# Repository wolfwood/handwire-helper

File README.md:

# Handwire Helpers

A collection of PCBs aimed at supporting handwired dactyl-ish keyboards. The goal is faster, simpler assembly (by offloading the key matrix from the handwiring to the PCB) and flexibility in placement of keys and connectors.

## Matrix PCBs

### Handwire Helper
Supports 8 columns, 4 rows for the first six columns and 5 for the last 2 (thumb) columns.  The first row is the pin towards the microcontroller connections (narrow side). On the MCU side there are 8 pins for the columns and 5 for the rows, with the final pin as an (unnecessary) ground.

The intent is to connect keyswitches to the PCB using hotswap sockets, soldered to [ribbon cables with DuPont connectors on the other side](https://www.adafruit.com/product/3141), which can plug in to the header on the long side of the PCB.

This lets the keyspacing be determined by a 3D printed case, independent of the PCB, so that electronics can be reused as keyboard designs change. This also means that different switch types can be supported, without prior consideration in the PCB design.

The microcontroller can be similarly connected to this board by jumpers, allowing flexibility in case design, and in placement of the USB plug.

Version 0.1 has been successfully manufactured and functionality has been tested and verified.

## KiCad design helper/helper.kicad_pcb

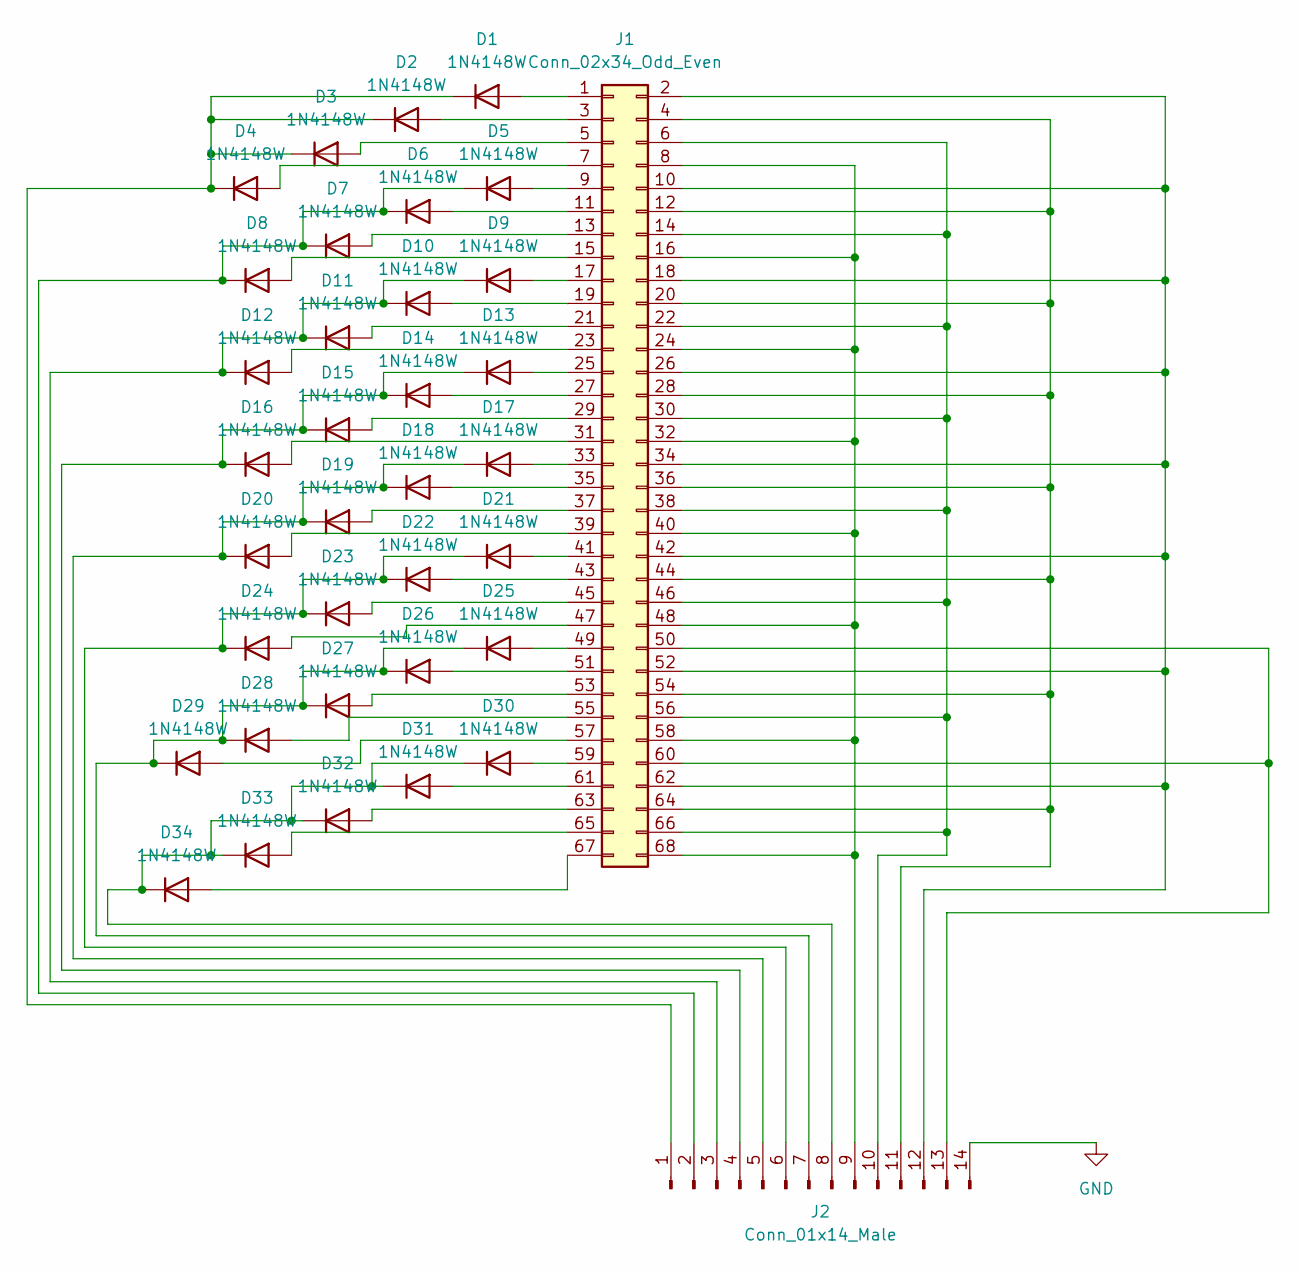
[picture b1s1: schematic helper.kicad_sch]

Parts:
D1, D2, D3, D4, D5, D6, D7, D8, D9, D10, D11, D12, D13, D14, D15, D16, D17, D18, D19, D20, D21, D22, D23, D24, D25, D26, D27, D28, D29, D30, D31, D32, D33, D34: 1N4148W; Reversable_Diode_SOD-123_THT
J1: Conn_02x34_Odd_Even; PinHeader_2x34_P2.54mm_Horizontal
J2: Conn_01x14_Male; PinHeader_2x07_P2.54mm_Horizontal

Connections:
GND: J2.14
unnamed: D1.1 (K), D2.1 (K), D3.1 (K), D4.1 (K), J2.1
unnamed: D1.2 (A), J1.1
unnamed: D2.2 (A), J1.3
unnamed: D3.2 (A), J1.5
unnamed: D4.2 (A), J1.7
unnamed: D5.1 (K), D6.1 (K), D7.1 (K), D8.1 (K), J2.2
unnamed: D5.2 (A), J1.9
unnamed: D6.2 (A), J1.11
unnamed: D7.2 (A), J1.13
unnamed: D8.2 (A), J1.15
unnamed: D9.2 (A), J1.17
unnamed: D9.1 (K), D10.1 (K), D11.1 (K), D12.1 (K), J2.3
unnamed: D10.2 (A), J1.19
unnamed: D11.2 (A), J1.21
unnamed: D12.2 (A), J1.23
unnamed: D13.1 (K), D14.1 (K), D15.1 (K), D16.1 (K), J2.4
unnamed: D13.2 (A), J1.25
unnamed: D14.2 (A), J1.27
unnamed: D15.2 (A), J1.29
unnamed: D16.2 (A), J1.31
unnamed: D17.1 (K), D18.1 (K), D19.1 (K), D20.1 (K), J2.5
unnamed: D17.2 (A), J1.33
unnamed: D18.2 (A), J1.35
unnamed: D19.2 (A), J1.37
unnamed: D20.2 (A), J1.39
unnamed: D21.1 (K), D22.1 (K), D23.1 (K), D24.1 (K), J2.6
unnamed: D21.2 (A), J1.41
unnamed: D22.2 (A), J1.43
unnamed: D23.2 (A), J1.45
unnamed: D24.2 (A), J1.47
unnamed: D25.1 (K), D26.1 (K), D27.1 (K), D28.1 (K), D29.1 (K), J2.7
unnamed: D25.2 (A), J1.49
unnamed: D26.2 (A), J1.51
unnamed: D27.2 (A), J1.53
unnamed: D28.2 (A), J1.55
unnamed: D29.2 (A), J1.57
unnamed: D30.1 (K), D31.1 (K), D32.1 (K), D33.1 (K), D34.1 (K), J2.8
unnamed: D30.2 (A), J1.59
unnamed: D31.2 (A), J1.61
unnamed: D32.2 (A), J1.63
unnamed: D33.2 (A), J1.65
unnamed: D34.2 (A), J1.67
unnamed: J1.2, J1.10, J1.18, J1.26, J1.34, J1.42, J1.52, J1.62, J2.12
unnamed: J1.4, J1.12, J1.20, J1.28, J1.36, J1.44, J1.54, J1.64, J2.11
unnamed: J1.6, J1.14, J1.22, J1.30, J1.38, J1.46, J1.56, J1.66, J2.10
unnamed: J1.8, J1.16, J1.24, J1.32, J1.40, J1.48, J1.58, J1.68, J2.9
unnamed: J1.50, J1.60, J2.13

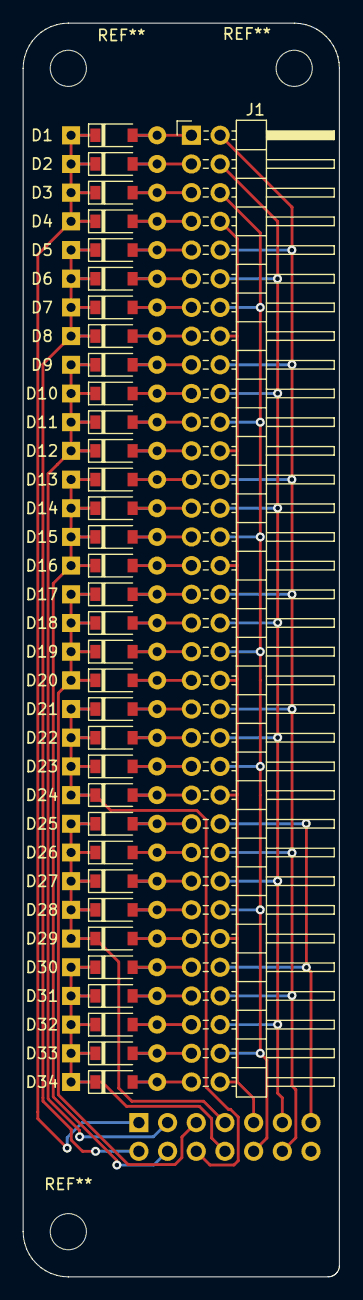
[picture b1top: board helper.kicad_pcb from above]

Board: 2 copper layers, 28.0 x 111.0 mm, 36 parts (1 on the bottom side), 47 nets.

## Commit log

2023-01-07 handwire helper with SOD-323's
2023-01-07 handwire helper for 4/5 x 8 standard matrix with through-hole diodes and ground fill
2023-01-08 consolidate row traces so they don't block the fill
2023-01-17 Handwire Helper version 0.1 as submitted
2023-01-17 README
2023-02-12 typo
2023-06-26 Update README.md to reflect that the design works
